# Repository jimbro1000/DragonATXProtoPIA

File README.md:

# Dragon 32 ATX Prototype PIA

This repository contains the KiCad project files
to produce the PIA component board for my
ATX Prototype backplane.

This design requires the ATX backplane board in order 
to operate
See https://github.com/jimbro1000/DragonATXProto

## Notes

Revision 1 includes the standard 2 PIAs but also
provides footprints for a dedicated ACIA, as used
on the Dragon 64, and a RTC. Both these extras
utilise the redundant address mappings for PIA 0.

The ACIA and PIA can be omitted without any impact
to the functioning of the computer while in Dragon 32
mode. The ACIA must be present for Dragon 64 mode.

This design has been completed using KiCad 9. Earlier
versions of KiCad are not compatible.

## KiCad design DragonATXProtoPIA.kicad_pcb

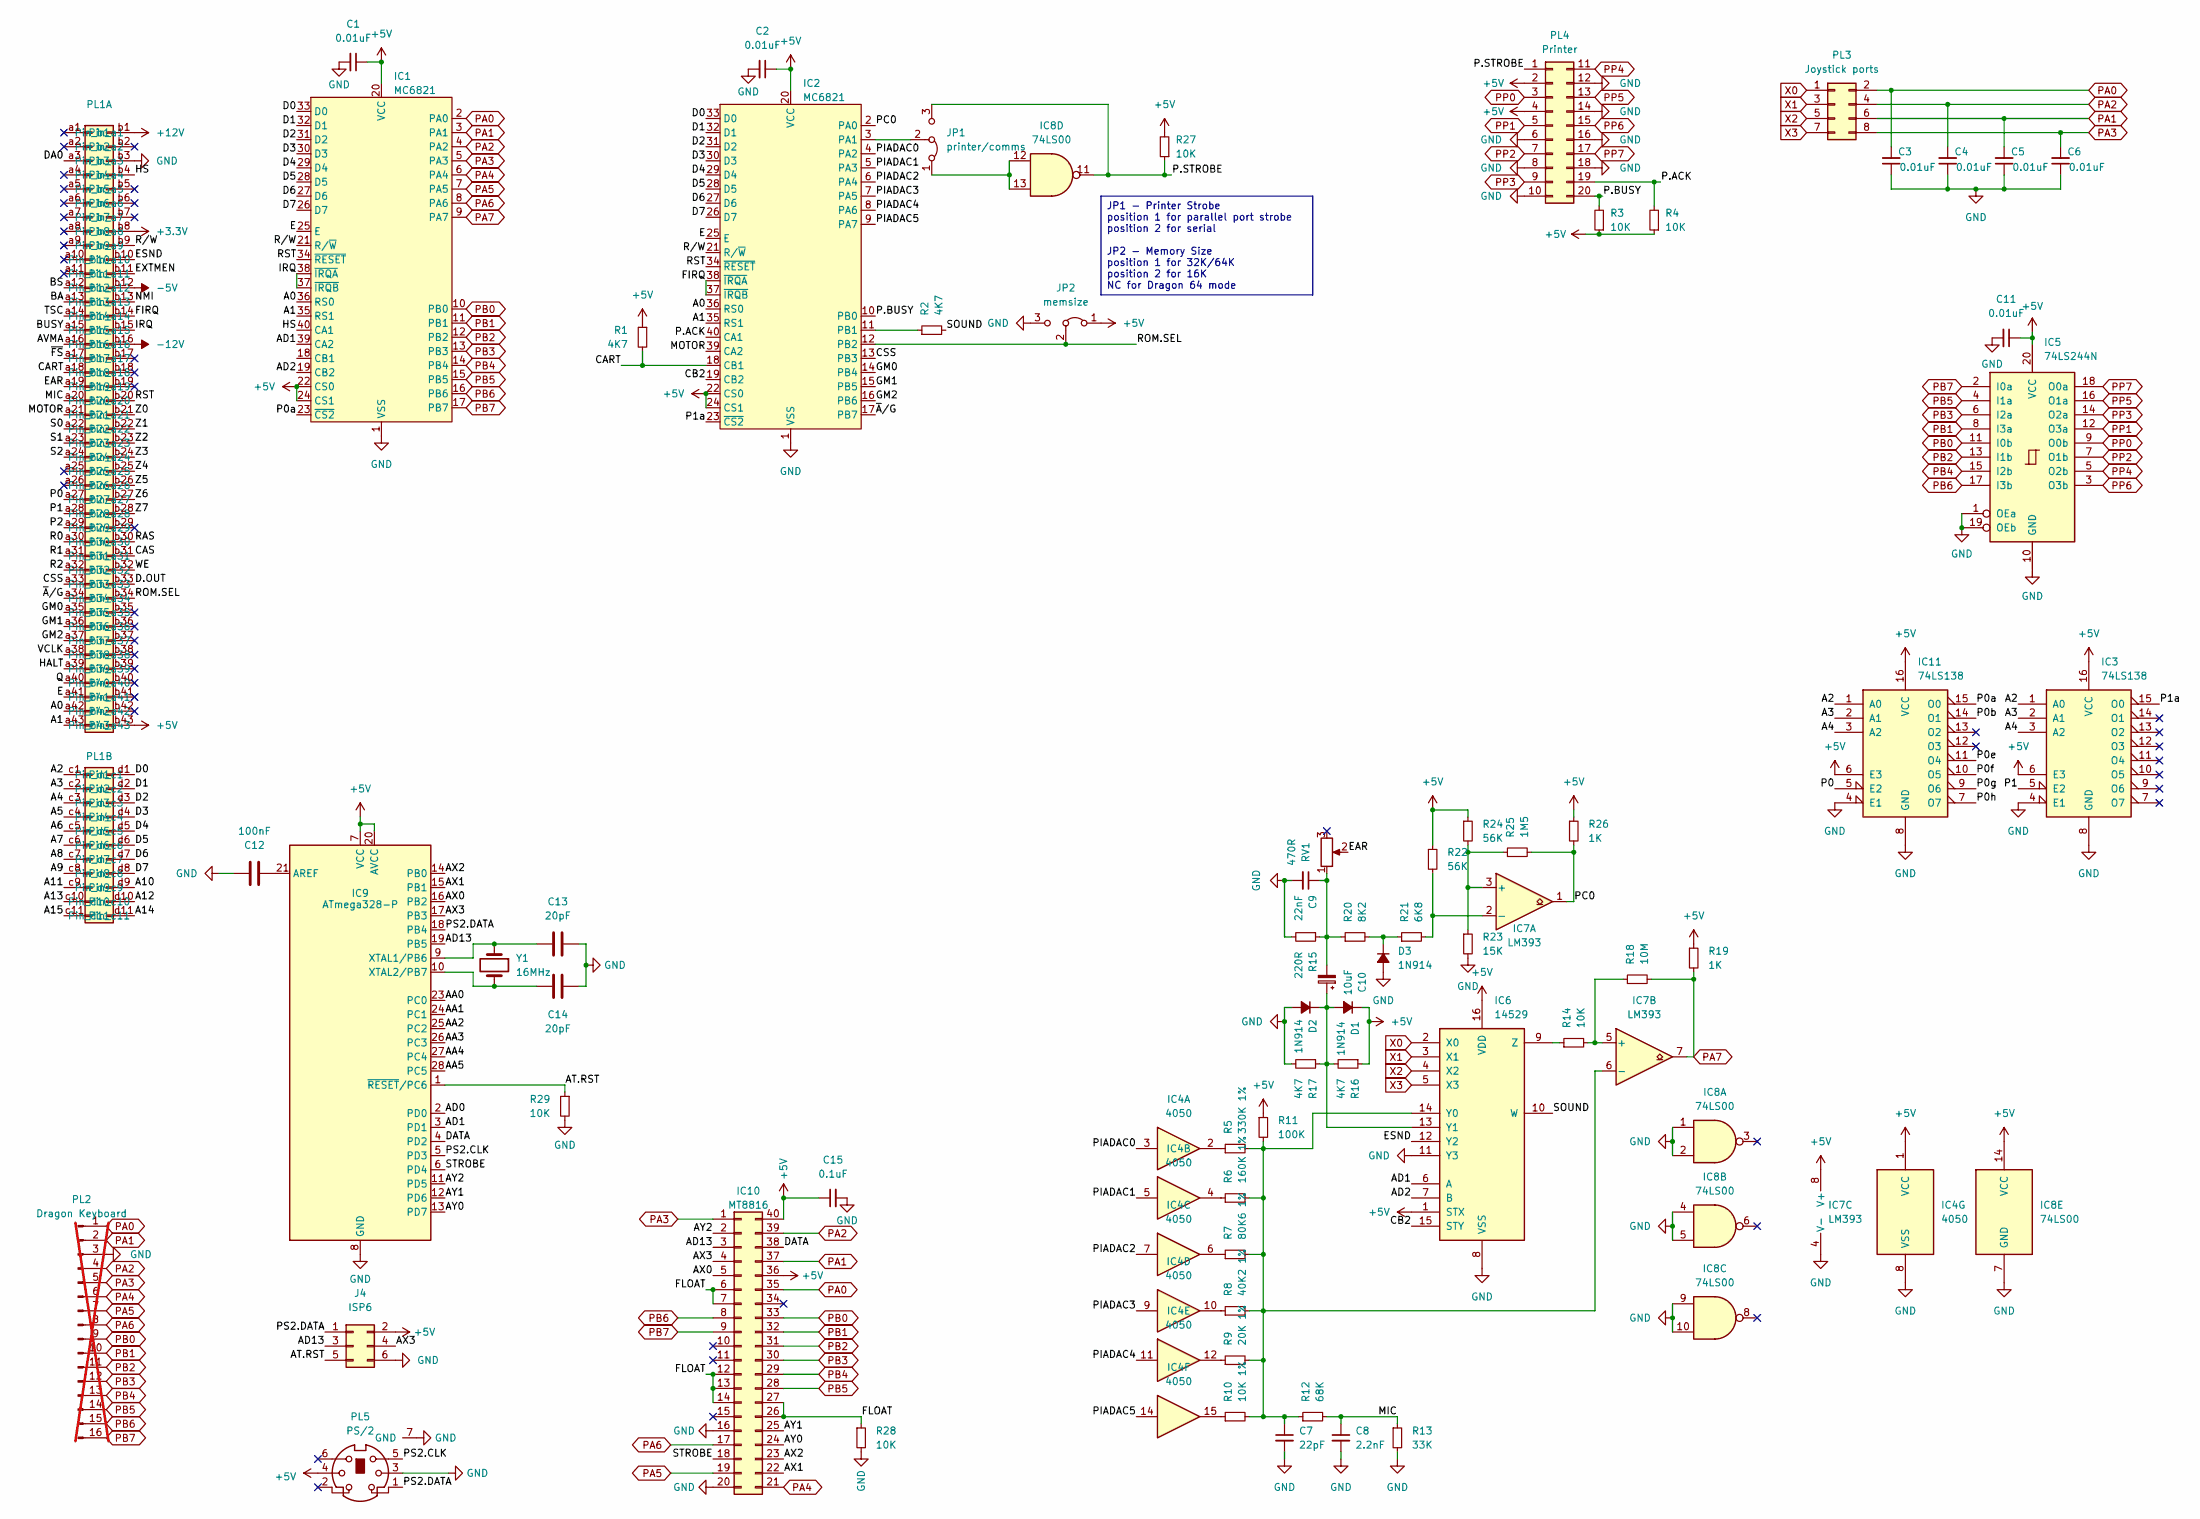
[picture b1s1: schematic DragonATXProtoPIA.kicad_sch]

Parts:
C1, C2, C11: 0.01uF; C_Disc_D4.3mm_W1.9mm_P5.00mm; DigiKey BC2662CT-ND
C3, C4, C5, C6: 0.01uF; C_Disc_D4.3mm_W1.9mm_P5.00mm; DigiKey BC1101CT-ND
C7: 22pF; C_Disc_D4.3mm_W1.9mm_P5.00mm; DigiKey BC2662CT-ND
C8: 2.2nF; C_Disc_D4.3mm_W1.9mm_P5.00mm; DigiKey BC2662CT-ND
C9: 22nF; C_Disc_D4.3mm_W1.9mm_P5.00mm; DigiKey BC2662CT-ND
C10: 10uF; CP_Radial_D6.3mm_P2.50mm
C12: 100nF; C_Disc_D3.0mm_W1.6mm_P2.50mm
C13, C14: 20pF; C_Disc_D3.0mm_W1.6mm_P2.50mm
C15: 0.1uF; C_Disc_D4.3mm_W1.9mm_P5.00mm; DigiKey BC2662CT-ND
D1, D2, D3: 1N914; D_DO-35_SOD27_P7.62mm_Horizontal; DigiKey 1N914FS-ND
IC1, IC2: MC6821; DIP-40_W15.24mm
IC3, IC11: 74LS138; DIP-16_W7.62mm
IC4: 4050; DIP-16_W7.62mm
IC5: 74LS244N; DIP-20_W7.62mm; DigiKey 296-1653-5-ND
IC6: 14529; DIP-16_W7.62mm
IC7: LM393; DIP-8_W7.62mm
IC8: 74LS00; DIP-14_W7.62mm
IC9: ATmega328-P; DIP-28_W7.62mm
IC10: MT8816; DIP-40_W15.24mm
J4: ISP6; PinHeader_2x03_P2.54mm_Vertical
JP1: printer/comms; PinHeader_1x03_P2.54mm_Vertical
JP2: memsize; PinHeader_1x03_P2.54mm_Vertical
PL1: Card_Edge
PL2: Dragon Keyboard; PinHeader_1x16_P2.54mm_Vertical; DigiKey 952-2521-ND; not fitted
PL3: Joystick ports; PinHeader_2x04_P2.54mm_Vertical
PL4: Printer; IDC-Header_2x10-1MP_P2.54mm_Latch_Horizontal; DigiKey CHR20G-ND
PL5: PS/2; Connector_DIN_Mini_Female_6
R1, R2, R16, R17: 4K7; R_Axial_DIN0207_L6.3mm_D2.5mm_P2.54mm_Vertical
R3, R4, R27: 10K; R_Axial_DIN0207_L6.3mm_D2.5mm_P2.54mm_Vertical; DigiKey CF14JT10K0CT-ND
R5: 330K 1%; R_Axial_DIN0207_L6.3mm_D2.5mm_P2.54mm_Vertical
R6: 160K 1%; R_Axial_DIN0207_L6.3mm_D2.5mm_P2.54mm_Vertical
R7: 80K6 1%; R_Axial_DIN0207_L6.3mm_D2.5mm_P2.54mm_Vertical
R8: 40K2 1%; R_Axial_DIN0207_L6.3mm_D2.5mm_P2.54mm_Vertical
R9: 20K 1%; R_Axial_DIN0207_L6.3mm_D2.5mm_P2.54mm_Vertical
R10: 10K 1%; R_Axial_DIN0207_L6.3mm_D2.5mm_P2.54mm_Vertical
R11: 100K; R_Axial_DIN0207_L6.3mm_D2.5mm_P2.54mm_Vertical
R12: 68K; R_Axial_DIN0207_L6.3mm_D2.5mm_P2.54mm_Vertical
R13: 33K; R_Axial_DIN0207_L6.3mm_D2.5mm_P2.54mm_Vertical
R14, R28, R29: 10K; R_Axial_DIN0207_L6.3mm_D2.5mm_P2.54mm_Vertical
R15: 220R; R_Axial_DIN0207_L6.3mm_D2.5mm_P2.54mm_Vertical
R18: 10M; R_Axial_DIN0207_L6.3mm_D2.5mm_P2.54mm_Vertical
R19, R26: 1K; R_Axial_DIN0207_L6.3mm_D2.5mm_P2.54mm_Vertical
R20: 8K2; R_Axial_DIN0207_L6.3mm_D2.5mm_P2.54mm_Vertical
R21: 6K8; R_Axial_DIN0207_L6.3mm_D2.5mm_P2.54mm_Vertical
R22, R24: 56K; R_Axial_DIN0207_L6.3mm_D2.5mm_P2.54mm_Vertical
R23: 15K; R_Axial_DIN0207_L6.3mm_D2.5mm_P2.54mm_Vertical
R25: 1M5; R_Axial_DIN0207_L6.3mm_D2.5mm_P2.54mm_Vertical
RV1: 470R; Potentiometer_Piher_PT-15-H05_Horizontal
Y1: 16MHz; Crystal_HC49-U_Vertical

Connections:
+3.3V: PL1.b8
+5V: C1.1, C2.1, C11.1, C15.1, D1.1 (K), IC1.20 (VCC), IC1.22 (CS0), IC1.24 (CS1), IC2.20 (VCC), IC2.22 (CS0), IC2.24 (CS1), IC3.6 (E3), IC3.16 (VCC), IC4.1 (VCC), IC5.20 (VCC), IC6.1 (STX), IC6.16 (VDD), IC7.8 (V+), IC8.14 (VCC), IC9.7 (VCC), IC9.20 (AVCC), IC10.36, IC10.40, IC11.6 (E3), IC11.16 (VCC), J4.2, JP2.1 (A), PL1.b43, PL4.2, PL4.4, PL5.4, R1.1, R3.1, R4.1, R11.1, R16.1, R19.1, R22.1, R24.1, R26.1, R27.2
+12V: PL1.b1
-5V: PL1.b12
-12V: PL1.b16
/A0: IC1.36 (RS0), IC2.36 (RS0), PL1.a42
/A1: IC1.35 (RS1), IC2.35 (RS1), PL1.a43
/A2: IC3.1 (A0), IC11.1 (A0), PL1.c1
/A3: IC3.2 (A1), IC11.2 (A1), PL1.c2
/A4: IC3.3 (A2), IC11.3 (A2), PL1.c3
/A5: PL1.c4
/A6: PL1.c5
/A7: PL1.c6
/A8: PL1.c7
/A9: PL1.c8
/A10: PL1.d9
/A11: PL1.c9
/A12: PL1.d10
/A13: PL1.c10
/A14: PL1.d11
/A15: PL1.c11
/AA0: IC9.23 (PC0)
/AA1: IC9.24 (PC1)
/AA2: IC9.25 (PC2)
/AA3: IC9.26 (PC3)
/AA4: IC9.27 (PC4)
/AA5: IC9.28 (PC5)
/AD0: IC9.2 (PD0)
/AD1: IC1.39 (CA2), IC6.6 (A), IC9.3 (PD1)
/AD2: IC1.19 (CB2), IC6.7 (B)
/AD13: IC9.19 (PB5), IC10.3, J4.3
/AT.RST: IC9.1 (~RESET/PC6), J4.5, R29.1
/AVMA: PL1.a16
/AX0: IC9.16 (PB2), IC10.5
/AX1: IC9.15 (PB1), IC10.22
/AX2: IC9.14 (PB0), IC10.23
/AX3: IC9.17 (PB3), IC10.4, J4.4
/AY0: IC9.13 (PD7), IC10.24
/AY1: IC9.12 (PD6), IC10.25
/AY2: IC9.11 (PD5), IC10.2
/BA: PL1.a13
/BS: PL1.a12
/BUSY: PL1.a15
/CART: IC2.18 (CB1), PL1.a18, R1.2
/CAS: PL1.b31
/CB2: IC2.19 (CB2), IC6.15 (STY)
/CSS: IC2.13 (PB3), PL1.a33
/D0: IC1.33 (D0), IC2.33 (D0), PL1.d1
/D1: IC1.32 (D1), IC2.32 (D1), PL1.d2
/D2: IC1.31 (D2), IC2.31 (D2), PL1.d3
/D3: IC1.30 (D3), IC2.30 (D3), PL1.d4
/D4: IC1.29 (D4), IC2.29 (D4), PL1.d5
/D5: IC1.28 (D5), IC2.28 (D5), PL1.d6
/D6: IC1.27 (D6), IC2.27 (D6), PL1.d7
/D7: IC1.26 (D7), IC2.26 (D7), PL1.d8
/D.OUT: PL1.b33
/DA0: PL1.a3
/DATA: IC9.4 (PD2), IC10.38
/E: IC1.25 (E), IC2.25 (E), PL1.a41
/EAR: PL1.a19, RV1.2
/ESND: IC6.12 (Y2), PL1.b10
/EXTMEN: PL1.b11
/FIRQ: IC2.37 (~IRQB), IC2.38 (~IRQA), PL1.b14
/FLOAT: IC10.6, IC10.7, IC10.12, IC10.13, IC10.14, IC10.26, IC10.27, R28.1
/GM0: IC2.14 (PB4), PL1.a35
/GM1: IC2.15 (PB5), PL1.a36
/GM2: IC2.16 (PB6), PL1.a37
/HALT: PL1.a39
/HS: IC1.40 (CA1), PL1.b4
/IRQ: IC1.37 (~IRQB), IC1.38 (~IRQA), PL1.b15
/MIC: C8.1, PL1.a20, R12.2, R13.1
/MOTOR: IC2.39 (CA2), PL1.a21
/NMI: PL1.b13
/P0: IC11.5 (E2), PL1.a27
/P0a: IC1.23 (~CS2), IC11.15 (O0)
/P0b: IC11.14 (O1)
/P0e: IC11.11 (O4)
/P0f: IC11.10 (O5)
/P0g: IC11.9 (O6)
/P0h: IC11.7 (O7)
/P1: IC3.5 (E2), PL1.a28
/P1a: IC2.23 (~CS2), IC3.15 (O0)
/P2: PL1.a29
/P.ACK: IC2.40 (CA1), PL4.19, R4.2
/P.BUSY: IC2.10 (PB0), PL4.20, R3.2
/P.STROBE: IC8.11, JP1.3 (B), PL4.1, R27.1
/PC0: IC2.2 (PA0), IC7.1, R25.2, R26.2
/PIADAC0: IC2.4 (PA2), IC4.3
/PIADAC1: IC2.5 (PA3), IC4.5
/PIADAC2: IC2.6 (PA4), IC4.7
/PIADAC3: IC2.7 (PA5), IC4.9
/PIADAC4: IC2.8 (PA6), IC4.11
/PIADAC5: IC2.9 (PA7), IC4.14
/PS2.CLK: IC9.5 (PD3), PL5.5
/PS2.DATA: IC9.18 (PB4), J4.1, PL5.1
/Q: PL1.a40
/R0: PL1.a30
/R1: PL1.a31
/R2: PL1.a32
/RAS: PL1.b30
/ROM.SEL: IC2.12 (PB2), JP2.2 (C), PL1.b34
/RST: IC1.34 (~RESET), IC2.34 (~RESET), PL1.b20
/R/W: IC1.21 (R/~W), IC2.21 (R/~W), PL1.b9
/S0: PL1.a22
/S1: PL1.a23
/S2: PL1.a24
/SOUND: IC6.10 (W), R2.2
/STROBE: IC9.6 (PD4), IC10.18
/TSC: PL1.a14
/VCLK: PL1.a38
/WE: PL1.b32
/Z0: PL1.b21
/Z1: PL1.b22
/Z2: PL1.b23
/Z3: PL1.b24
/Z4: PL1.b25
/Z5: PL1.b26
/Z6: PL1.b27
/Z7: PL1.b28
/~A/G: IC2.17 (PB7), PL1.a34
/~FS: PL1.a17
GND: C1.2, C2.2, C3.1, C4.1, C5.1, C6.1, C7.2, C8.2, C9.2, C11.2, C12.2, C13.2, C14.2, C15.2, D2.2 (A), D3.2 (A), IC1.1 (VSS), IC2.1 (VSS), IC3.4 (E1), IC3.8 (GND), IC4.8 (VSS), IC5.1 (OEa), IC5.10 (GND), IC5.19 (OEb), IC6.8 (VSS), IC6.11 (Y3), IC7.4 (V-), IC8.1, IC8.2, IC8.4, IC8.5, IC8.7 (GND), IC8.9, IC8.10, IC9.8 (GND), IC9.22 (GND), IC10.16, IC10.20, IC11.4 (E1), IC11.8 (GND), J4.6, JP2.3 (B), PL1.b3, PL2.3, PL4.6, PL4.8, PL4.10, PL4.12, PL4.14, PL4.16, PL4.18, PL5.3, PL5.7 (GND), R13.2, R15.2, R17.2, R23.2, R28.2, R29.2
unnamed: C9.1, C10.2, R15.1, R20.1, RV1.1
unnamed: C10.1, D1.2 (A), D2.1 (K), IC6.13 (Y1), R16.2, R17.1
unnamed: D3.1 (K), R20.2, R21.1
unnamed: IC2.3 (PA1), JP1.2 (C)
unnamed: IC2.11 (PB1), R2.1
unnamed: IC4.2, R5.1
unnamed: IC4.4, R6.1
unnamed: IC4.6, R7.1
unnamed: IC4.10, R8.1
unnamed: IC4.12, R9.1
unnamed: IC4.15, R10.1
unnamed: C7.1, IC6.14 (Y0), IC7.6 (-), R5.2, R6.2, R7.2, R8.2, R9.2, R10.2, R11.2, R12.1
unnamed: IC6.9 (Z), R14.1
unnamed: IC7.3 (+), R23.1, R24.2, R25.1
unnamed: IC7.2 (-), R21.2, R22.2
unnamed: IC7.5 (+), R14.2, R18.1
unnamed: C12.1, IC9.21 (AREF)
unnamed: C13.1, IC9.9 (XTAL1/PB6), Y1.1
unnamed: C14.1, IC9.10 (XTAL2/PB7), Y1.2
unnamed: IC8.12, IC8.13, JP1.1 (A)
PA0: C3.2, IC1.2 (PA0), IC10.35, PL2.1, PL3.2
PA1: C5.2, IC1.3 (PA1), IC10.37, PL2.2, PL3.6
PA2: C4.2, IC1.4 (PA2), IC10.39, PL2.4, PL3.4
PA3: C6.2, IC1.5 (PA3), IC10.1, PL2.5, PL3.8
PA4: IC1.6 (PA4), IC10.21, PL2.6
PA5: IC1.7 (PA5), IC10.19, PL2.7
PA6: IC1.8 (PA6), IC10.17, PL2.8
PA7: IC1.9 (PA7), IC7.7, R18.2, R19.2
PB0: IC1.10 (PB0), IC5.11 (I0b), IC10.33, PL2.9
PB1: IC1.11 (PB1), IC5.8 (I3a), IC10.32, PL2.10
PB2: IC1.12 (PB2), IC5.13 (I1b), IC10.31, PL2.11
PB3: IC1.13 (PB3), IC5.6 (I2a), IC10.30, PL2.12
PB4: IC1.14 (PB4), IC5.15 (I2b), IC10.29, PL2.13
PB5: IC1.15 (PB5), IC5.4 (I1a), IC10.28, PL2.14
PB6: IC1.16 (PB6), IC5.17 (I3b), IC10.8, PL2.15
PB7: IC1.17 (PB7), IC5.2 (I0a), IC10.9, PL2.16
PP0: IC5.9 (O0b), PL4.3
PP1: IC5.12 (O3a), PL4.5
PP2: IC5.7 (O1b), PL4.7
PP3: IC5.14 (O2a), PL4.9
PP4: IC5.5 (O2b), PL4.11
PP5: IC5.16 (O1a), PL4.13
PP6: IC5.3 (O3b), PL4.15
PP7: IC5.18 (O0a), PL4.17
X0: IC6.2 (X0), PL3.1
X1: IC6.3 (X1), PL3.3
X2: IC6.4 (X2), PL3.5
X3: IC6.5 (X3), PL3.7

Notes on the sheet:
JP1 - Printer Strobe position 1 for parallel port strobe position 2 for serial JP2 - Memory Size position 1 for 32K/64K position 2 for 16K NC for Dragon 64 mode

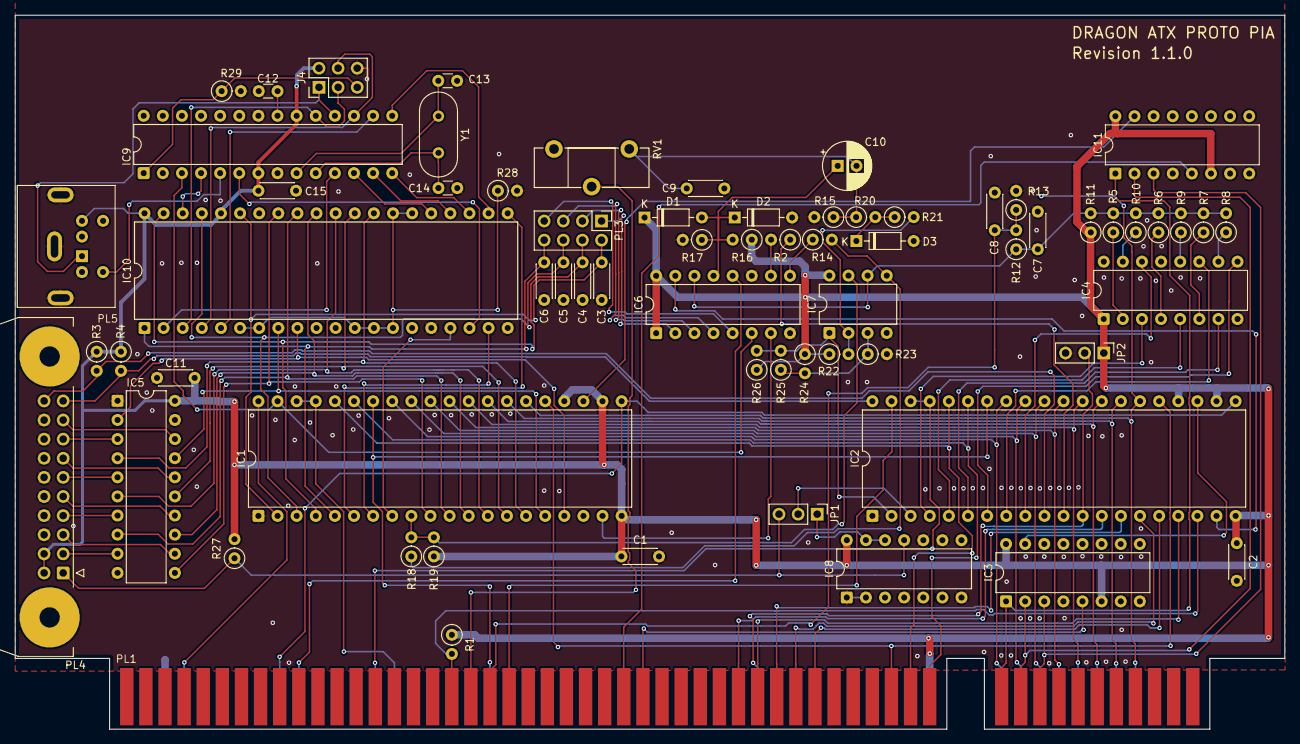
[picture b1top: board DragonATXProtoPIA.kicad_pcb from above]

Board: 2 copper layers, 168.7 x 94.9 mm, 67 parts (0 on the bottom side), 112 nets.

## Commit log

2025-03-18 upgrade card edge spec
2025-03-24 prepare for fabrication
2025-05-07 Rectify slot edge and vertical dimensions
2025-05-07 shrink board
2025-05-08 shrink dimensions
2025-05-08 remove uart and rtc
